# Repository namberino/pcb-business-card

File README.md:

# PCB Business Card

This is my custom PCB business card. I wanted to learn more about PCB design so a decided to make a fully custom PCB that functions both as a microcontroller and a business card.

> Note: *PCB_biz-card_3* is the final version of this project. The other 2 were just me messing around with the EDA

This is how it looks like:

I used EasyEDA to design the board. This was a big learning experience for me so the design doesn't follow the best practices but for now, it's good enough. This is the schematic and x-ray view of the board:

# Plans

Current plan: Move project into KiCAD

I plan on improving on this design. Here's a couple bullet points on what I plan on improving:

- Add an NFC antenna
- Use SMD components (Right now, I don't really have good access to many SMD components so the components I use are all through-hole)
- Add 5V battery to provide energy for the MCU

# Credits

This project was inspired by these projects:

- Xander Naumenko's [PCB business card](https://github.com/misprit7/PCB-Business-Card)
- Anthony Kouttron's [PCB business card](https://github.com/anthonykouttron/pcb-business-card-qr-nfc)
- Badr Bouslikhin's [Enchanté card](https://github.com/badrbouslikhin/Enchante)

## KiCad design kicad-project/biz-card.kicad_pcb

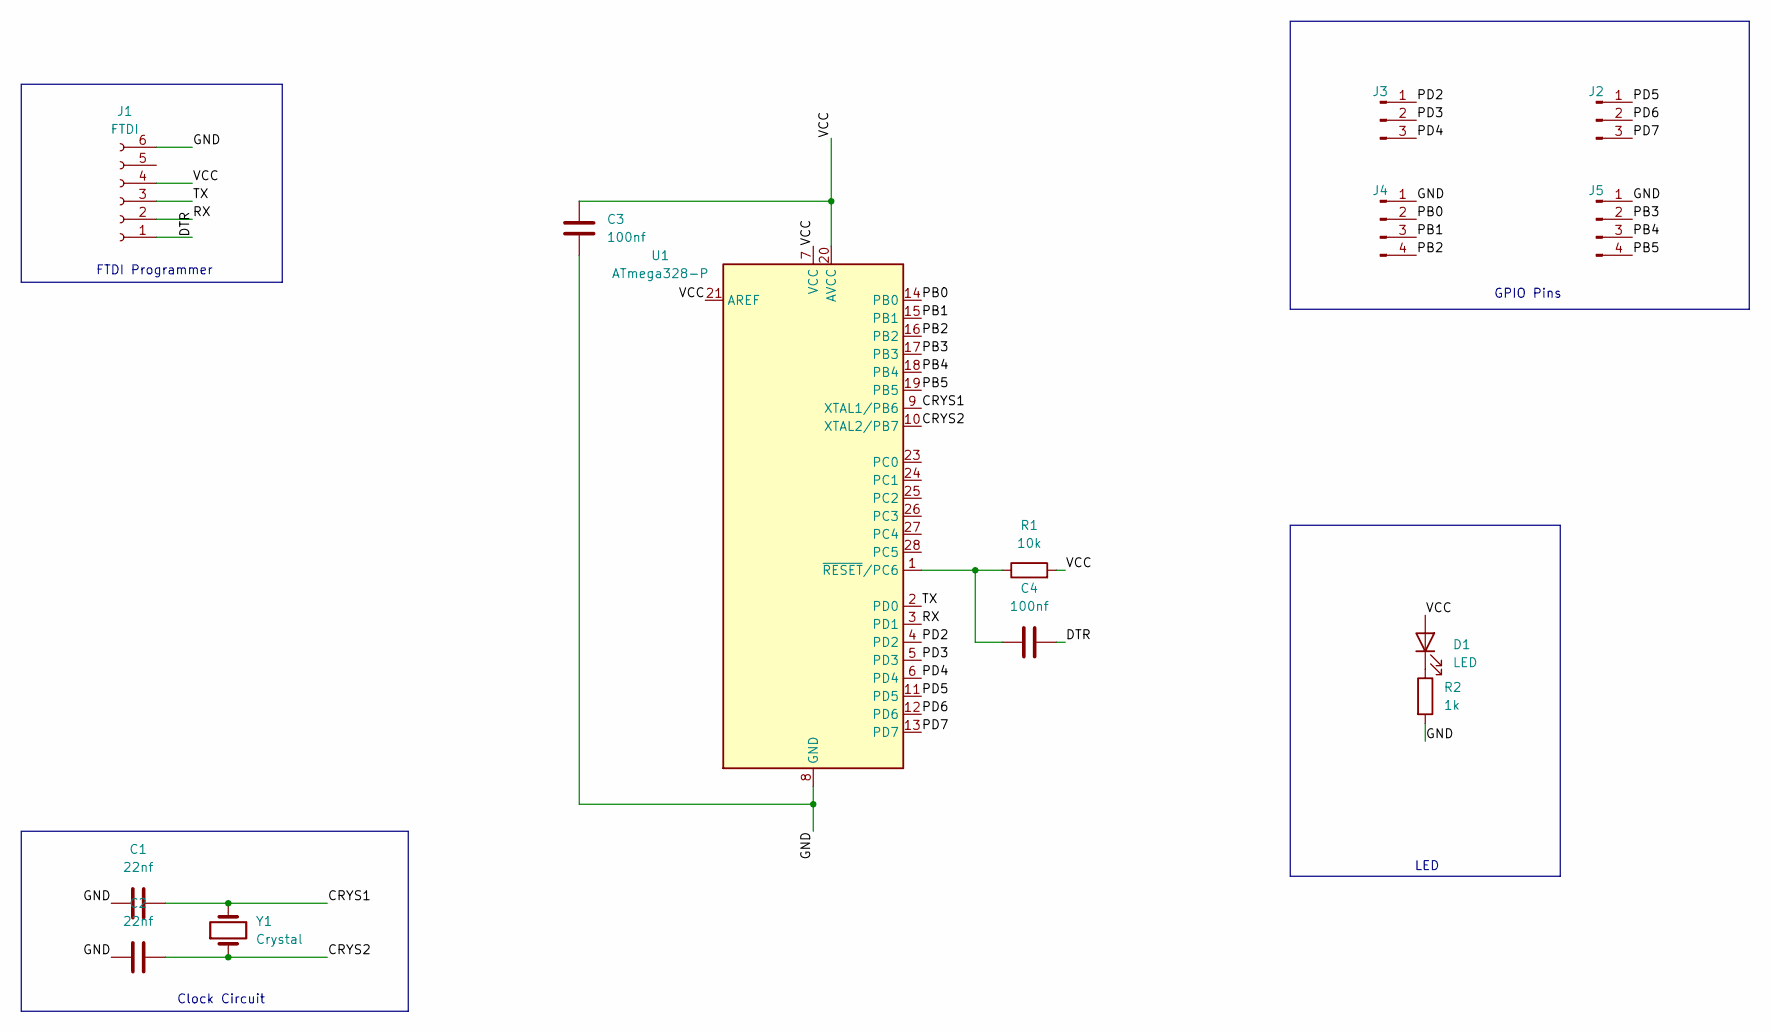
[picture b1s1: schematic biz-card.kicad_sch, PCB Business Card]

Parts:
C1, C2: 22nf; C_Axial_L3.8mm_D2.6mm_P7.50mm_Horizontal
C3: 100nf; C_Axial_L3.8mm_D2.6mm_P10.00mm_Horizontal
C4: 100nf; C_Axial_L3.8mm_D2.6mm_P7.50mm_Horizontal
D1: LED; LED_1206_3216Metric_Pad1.42x1.75mm_HandSolder
J1: FTDI; Hirose_DF13-06P-1.25DS_1x06_P1.25mm_Horizontal
J2, J3: Harwin_M20-89003xx_1x03_P2.54mm_Horizontal
J4, J5: Harwin_M20-89004xx_1x04_P2.54mm_Horizontal
R1: 10k; R_Axial_DIN0204_L3.6mm_D1.6mm_P5.08mm_Horizontal
R2: 1k; R_Axial_DIN0204_L3.6mm_D1.6mm_P5.08mm_Horizontal
U1: ATmega328-P; DIP-28_W7.62mm
Y1: Crystal; Crystal_HC18-U_Vertical

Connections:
/CRYS1: C1.2, U1.9 (XTAL1/PB6), Y1.2
/CRYS2: C2.2, U1.10 (XTAL2/PB7), Y1.1
/DTR: C4.2, J1.1
/GND: C1.1, C2.1, C3.1, J1.6, J4.1, J5.1, R2.2, U1.8 (GND), U1.22 (GND)
/PB0: J4.2, U1.14 (PB0)
/PB1: J4.3, U1.15 (PB1)
/PB2: J4.4, U1.16 (PB2)
/PB3: J5.2, U1.17 (PB3)
/PB4: J5.3, U1.18 (PB4)
/PB5: J5.4, U1.19 (PB5)
/PD2: J3.1, U1.4 (PD2)
/PD3: J3.2, U1.5 (PD3)
/PD4: J3.3, U1.6 (PD4)
/PD5: J2.1, U1.11 (PD5)
/PD6: J2.2, U1.12 (PD6)
/PD7: J2.3, U1.13 (PD7)
/RX: J1.2, U1.3 (PD1)
/TX: J1.3, U1.2 (PD0)
/VCC: C3.2, D1.2 (A), J1.4, R1.2, U1.7 (VCC), U1.20 (AVCC), U1.21 (AREF)
unnamed: D1.1 (K), R2.1
unnamed: C4.1, R1.1, U1.1 (~RESET/PC6)

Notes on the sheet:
FTDI Programmer
GPIO Pins
LED
Clock Circuit

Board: 2 copper layers, 14 parts (0 on the bottom side), 21 nets, no tracks yet.

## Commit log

2024-04-29 Literally everything
2024-04-29 Move pcb and schematic files to easyeda-project folder
2024-04-29 Add README.md
2024-04-29 Update README.md with details about the project
2024-04-29 Create LICENSE
2024-04-30 Update schematic readability and pcb layout
2024-04-30 Update README.md with new schematic and pcb layout
2024-04-30 Update README.md with note about final version
2024-04-30 Update README.md credit section
2024-04-30 Fix spacing and typo in README.md
2024-04-30 Fix typo in README.md
2024-06-08 Add kicad project directory
2024-06-23 Update LICENSE
